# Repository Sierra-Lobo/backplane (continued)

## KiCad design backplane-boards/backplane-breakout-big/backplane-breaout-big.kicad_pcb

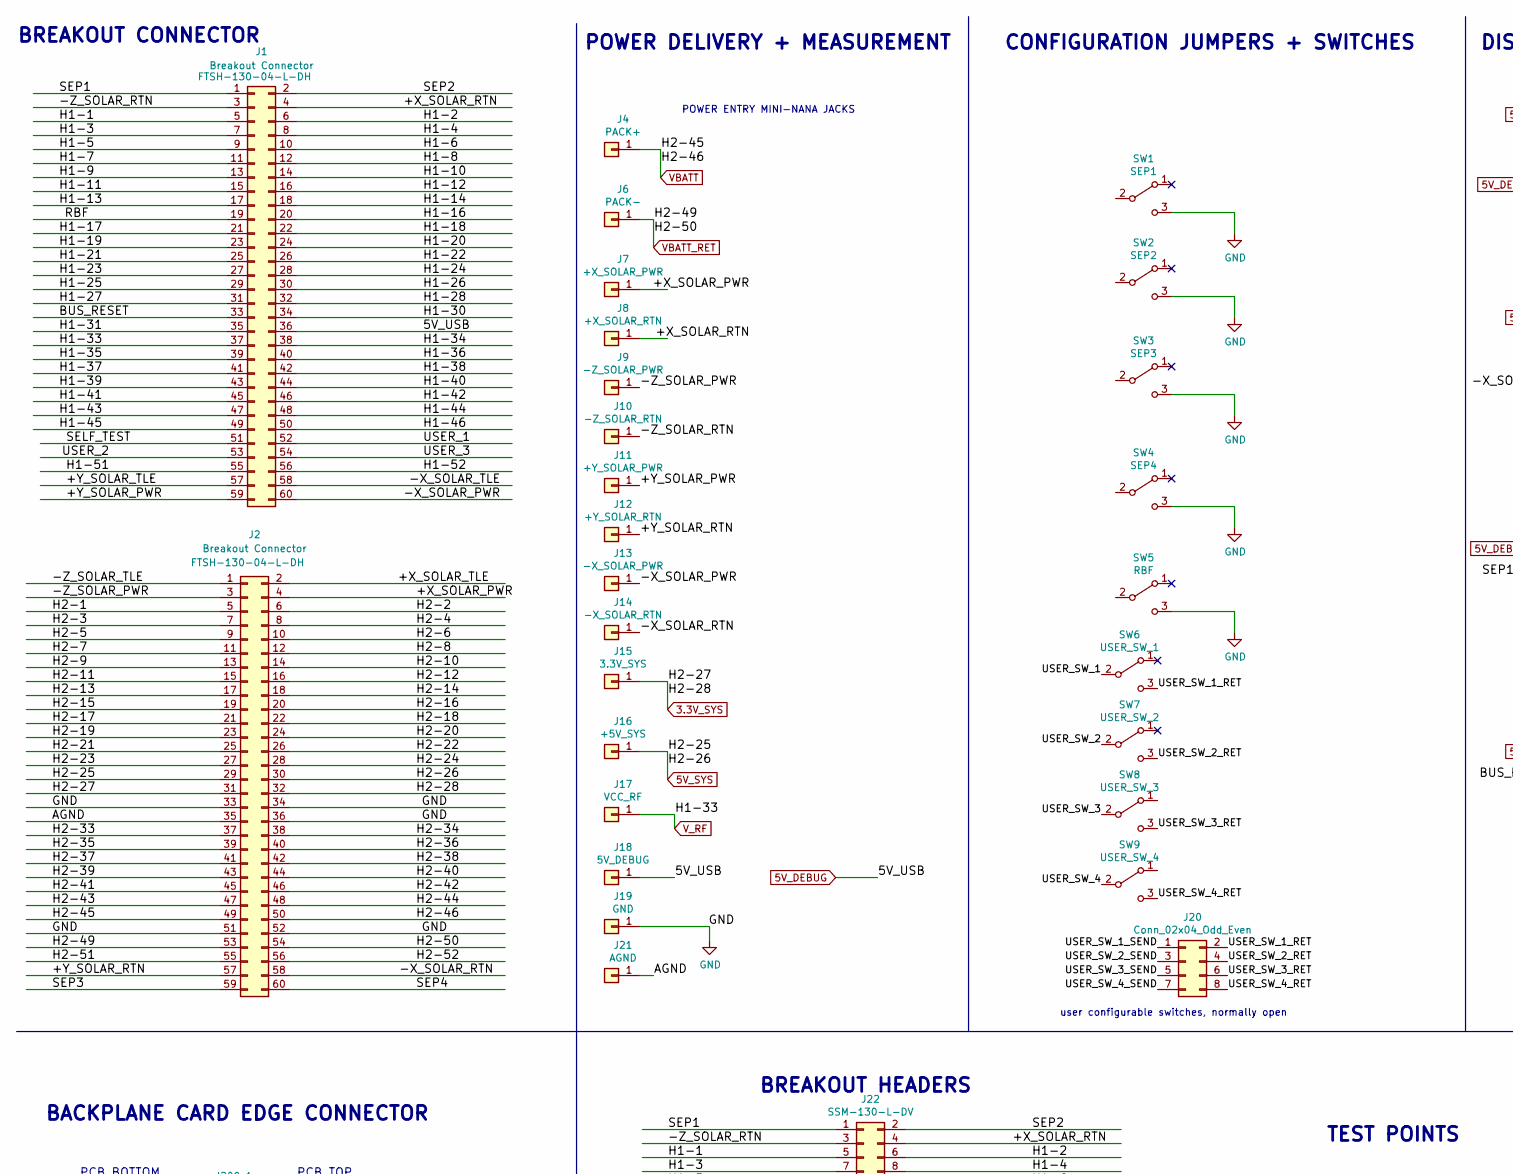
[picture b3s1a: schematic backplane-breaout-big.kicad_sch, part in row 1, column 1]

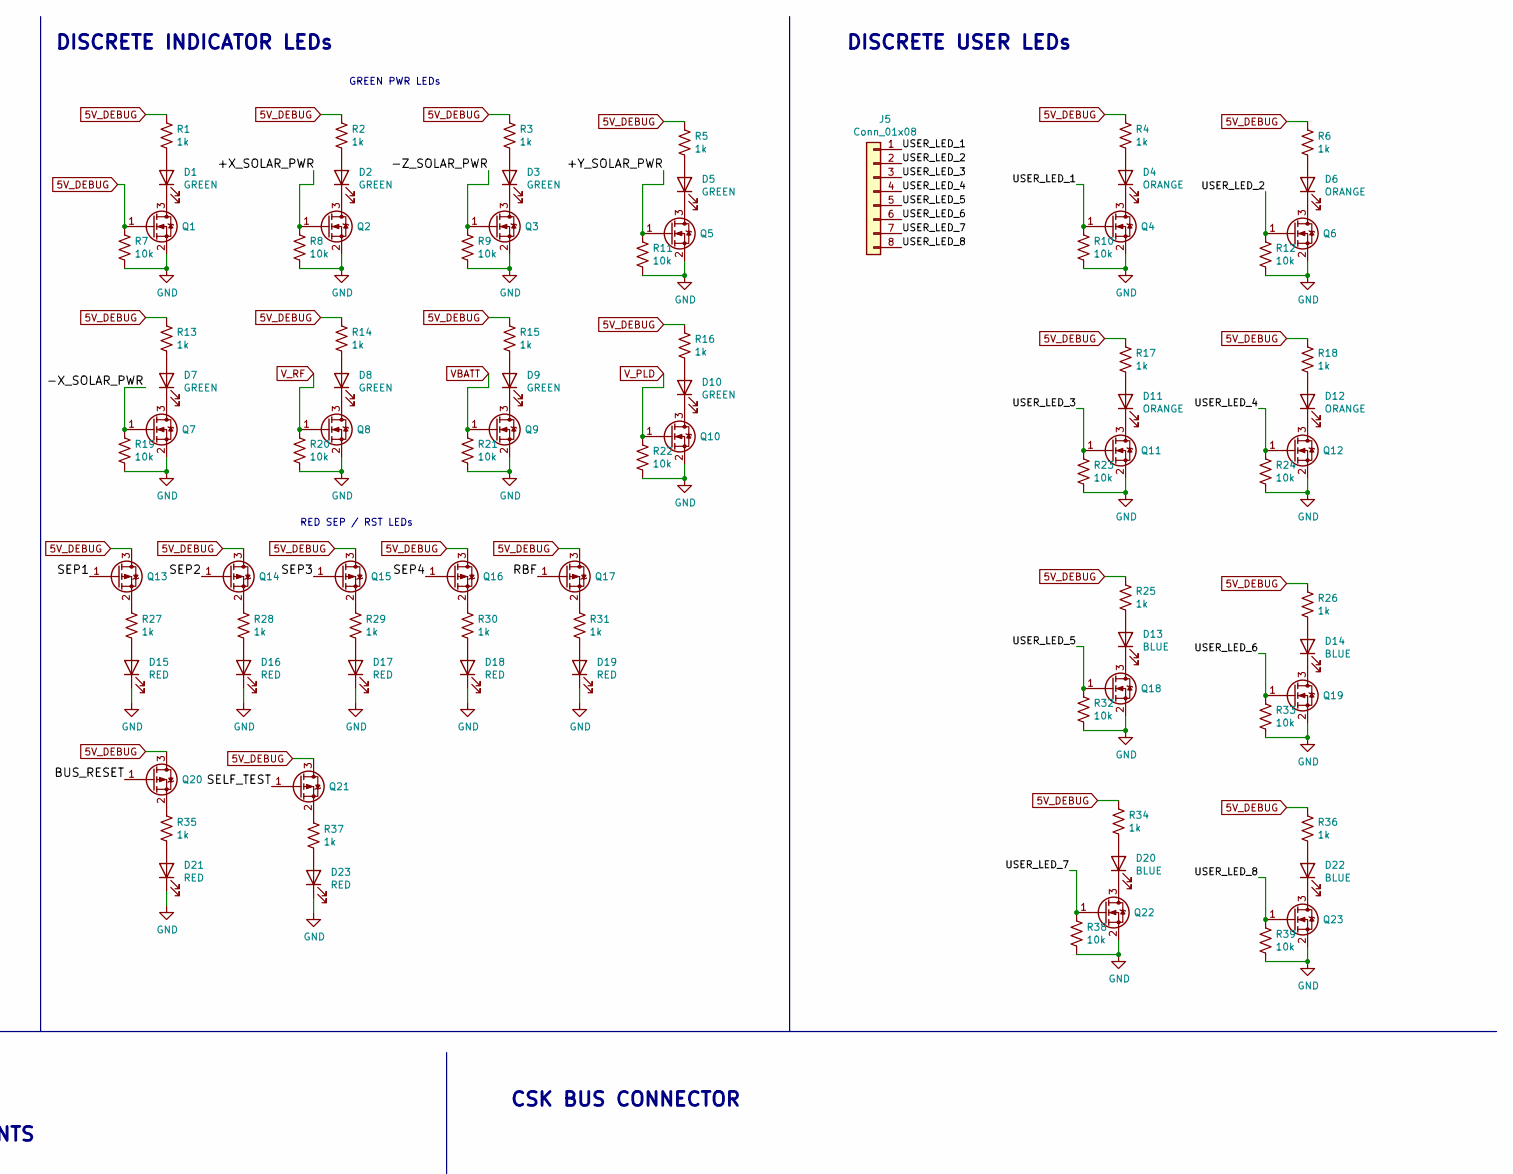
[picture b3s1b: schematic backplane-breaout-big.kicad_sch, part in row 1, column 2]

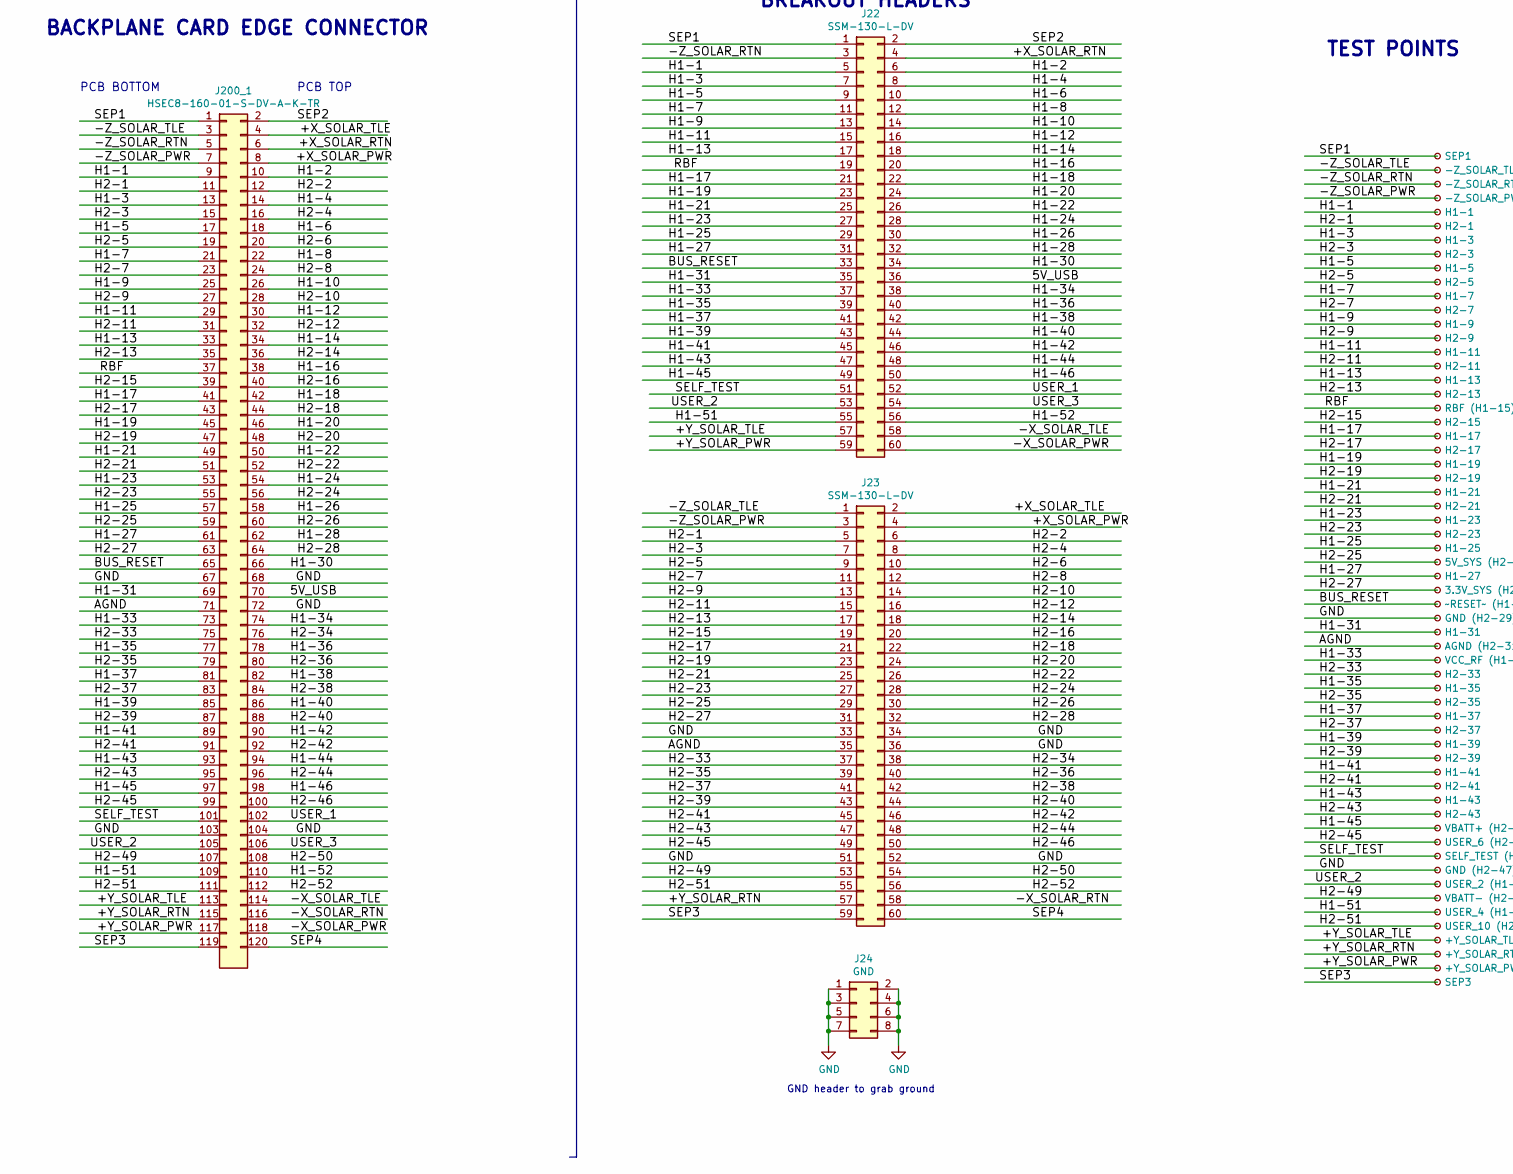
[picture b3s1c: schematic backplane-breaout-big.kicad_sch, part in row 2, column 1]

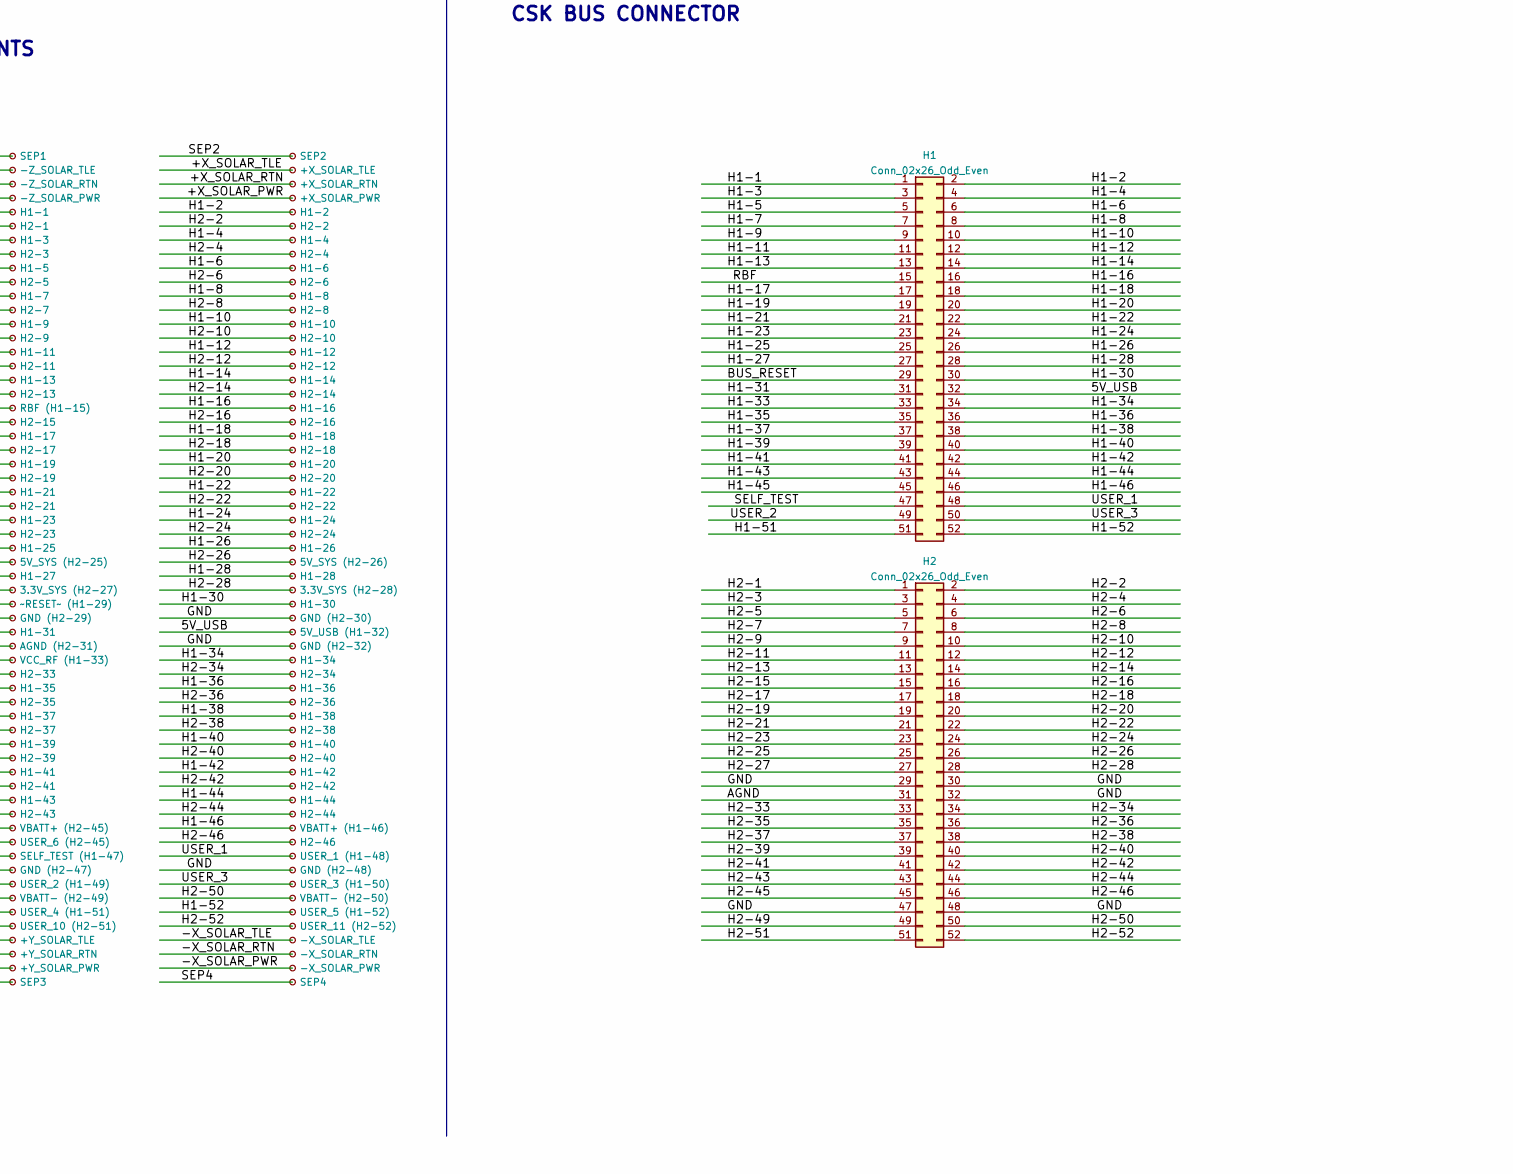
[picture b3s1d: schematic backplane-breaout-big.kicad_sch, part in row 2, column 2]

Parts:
D1, D2, D3, D5, D7, D8, D9, D10: GREEN; LED_0603_1608Metric_Castellated
D4, D6, D11, D12: ORANGE; LED_0603_1608Metric_Castellated
D13, D14, D20, D22: BLUE; LED_0603_1608Metric_Castellated
D15, D16, D17, D18, D19, D21, D23: RED; LED_0603_1608Metric_Castellated
H1, H2: Conn_02x26_Odd_Even; PinHeader_2x26_P2.54mm_Vertical
J1: Breakout Connector; SAMTEC_FTSH-130-04-L-DH; Manufacturer Part Numbe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 FTSH-130-04-L-DH
J2: Breakout Connector; SAMTEC_FTSH-130-04-L-DH_flipped; Manufacturer Part Numbe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 FTSH-130-04-L-DH
J4: PACK+; Keystone_476
J5: Conn_01x08; PinHeader_2x04_P2.54mm_Vertical_SMD
J6: PACK-; Keystone_476
J7: +X_SOLAR_PWR; Keystone_476
J8: +X_SOLAR_RTN; Keystone_476
J9: -Z_SOLAR_PWR; Keystone_476
J10: -Z_SOLAR_RTN; Keystone_476
J11: +Y_SOLAR_PWR; Keystone_476
J12: +Y_SOLAR_RTN; Keystone_476
J13: -X_SOLAR_PWR; Keystone_476
J14: -X_SOLAR_RTN; Keystone_476
J15: 3.3V_SYS; Keystone_476
J16: +5V_SYS; Keystone_476
J17: VCC_RF; Keystone_476
J18: 5V_DEBUG; Keystone_476
J19: GND; Keystone_476
J20: Conn_02x04_Odd_Even; PinHeader_2x04_P2.54mm_Vertical_SMD
J21: AGND; Keystone_476
J22, J23: SSM-130-L-DV; SAMTEC_SSM-130-L-DV
J24: GND; PinHeader_2x04_P2.54mm_Vertical_SMD
J200_1: HSEC8-160-01-S-DV-A-K-TR; Manufacturer Part Numbe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 HSEC8-160-01-S-DV-A-K-TR
Q1, Q2, Q3, Q4, Q5, Q6, Q7, Q8, Q9, Q10, Q11, Q12, Q18, Q19, Q22, Q23: DMG1012UW-7; SOT-323_SC-70
Q13, Q14, Q15, Q16, Q17, Q20, Q21: BSS84W-7-F; SOT-323_SC-70
R1, R2, R3, R4, R5, R6, R13, R14, R15, R16, R17, R18, R25, R26, R27, R28, R29, R30, R31, R34, R35, R36, R37: 1k; R_0603_1608Metric
R7, R8, R9, R10, R11, R12, R19, R20, R21, R22, R23, R24, R32, R33, R38, R39: 10k; R_0603_1608Metric
SW1: SEP1; JS102011SCQN
SW2: SEP2; JS102011SCQN
SW3: SEP3; JS102011SCQN
SW4: SEP4; JS102011SCQN
SW5: RBF; JS102011SCQN
SW6: USER_SW_1; JS102011SCQN
SW7: USER_SW_2; JS102011SCQN
SW8: USER_SW_3; JS102011SCQN
SW9: USER_SW_4; JS102011SCQN
TP1: SEP1; Keystone_5027
TP2: SEP2; Keystone_5027
TP3: -Z_SOLAR_TLE; Keystone_5027
TP4: +X_SOLAR_TLE; Keystone_5027
TP5: -Z_SOLAR_RTN; Keystone_5027
TP6: +X_SOLAR_RTN; Keystone_5027
TP7: -Z_SOLAR_PWR; Keystone_5027
TP8: +X_SOLAR_PWR; Keystone_5027
TP9: H1-1; Keystone_5027
TP10: H1-2; Keystone_5027
TP11: H2-1; Keystone_5027
TP12: H2-2; Keystone_5027
TP13: H1-3; Keystone_5027
TP14: H1-4; Keystone_5027
TP15: H2-3; Keystone_5027
TP16: H2-4; Keystone_5027
TP17: H1-5; Keystone_5027
TP18: H1-6; Keystone_5027
TP19: H2-5; Keystone_5027
TP20: H2-6; Keystone_5027
TP21: H1-7; Keystone_5027
TP22: H1-8; Keystone_5027
TP23: H2-7; Keystone_5027
TP24: H2-8; Keystone_5027
TP25: H1-9; Keystone_5027
TP26: H1-10; Keystone_5027
TP27: H2-9; Keystone_5027
TP28: H2-10; Keystone_5027
TP29: H1-11; Keystone_5027
TP30: H1-12; Keystone_5027
TP31: H2-11; Keystone_5027
TP32: H2-12; Keystone_5027
TP33: H1-13; Keystone_5027
TP34: H1-14; Keystone_5027
TP35: H2-13; Keystone_5027
TP36: H2-14; Keystone_5027
TP37: RBF (H1-15); Keystone_5027
TP38: H1-16; Keystone_5027
TP39: H2-15; Keystone_5027
TP40: H2-16; Keystone_5027
TP41: H1-17; Keystone_5027
TP42: H1-18; Keystone_5027
TP43: H2-17; Keystone_5027
TP44: H2-18; Keystone_5027
TP45: H1-19; Keystone_5027
TP46: H1-20; Keystone_5027
TP47: H2-19; Keystone_5027
TP48: H2-20; Keystone_5027
TP49: H1-21; Keystone_5027
TP50: H1-22; Keystone_5027
TP51: H2-21; Keystone_5027
TP52: H2-22; Keystone_5027
TP53: H1-23; Keystone_5027
TP54: H1-24; Keystone_5027
TP55: H2-23; Keystone_5027
TP56: H2-24; Keystone_5027
TP57: H1-25; Keystone_5027
TP58: H1-26; Keystone_5027
TP59: 5V_SYS (H2-25); Keystone_5027
TP60: 5V_SYS (H2-26); Keystone_5027
TP61: H1-27; Keystone_5027
TP62: H1-28; Keystone_5027
TP63: 3.3V_SYS (H2-27); Keystone_5027
TP64: 3.3V_SYS (H2-28); Keystone_5027
TP65: ~RESET~ (H1-29); Keystone_5027
TP66: H1-30; Keystone_5027
TP67: GND (H2-29); Keystone_5027
TP68: GND (H2-30); Keystone_5027
TP69: H1-31; Keystone_5027
TP70: 5V_USB (H1-32); Keystone_5027
TP71: AGND (H2-31); Keystone_5027
TP72: GND (H2-32); Keystone_5027
TP73: VCC_RF (H1-33); Keystone_5027
TP74: H1-34; Keystone_5027
TP75: H2-33; Keystone_5027
TP76: H2-34; Keystone_5027
TP77: H1-35; Keystone_5027
TP78: H1-36; Keystone_5027
TP79: H2-35; Keystone_5027
TP80: H2-36; Keystone_5027
TP81: H1-37; Keystone_5027
TP82: H1-38; Keystone_5027
TP83: H2-37; Keystone_5027
TP84: H2-38; Keystone_5027
TP85: H1-39; Keystone_5027
TP86: H1-40; Keystone_5027
TP87: H2-39; Keystone_5027
TP88: H2-40; Keystone_5027
TP89: H1-41; Keystone_5027
TP90: H1-42; Keystone_5027
TP91: H2-41; Keystone_5027
TP92: H2-42; Keystone_5027
TP93: H1-43; Keystone_5027
TP94: H1-44; Keystone_5027
TP95: H2-43; Keystone_5027
TP96: H2-44; Keystone_5027
TP97: VBATT+ (H2-45); Keystone_5027
TP98: VBATT+ (H1-46); Keystone_5027
TP99: USER_6 (H2-45); Keystone_5027
TP100: H2-46; Keystone_5027
TP101: SELF_TEST (H1-47); Keystone_5027
TP102: USER_1 (H1-48); Keystone_5027
TP103: GND (H2-47); Keystone_5027
TP104: GND (H2-48); Keystone_5027
TP105: USER_2 (H1-49); Keystone_5027
TP106: USER_3 (H1-50); Keystone_5027
TP107: VBATT- (H2-49); Keystone_5027
TP108: VBATT- (H2-50); Keystone_5027
TP109: USER_4 (H1-51); Keystone_5027
TP110: USER_5 (H1-52); Keystone_5027
TP111: USER_10 (H2-51); Keystone_5027
TP112: USER_11 (H2-52); Keystone_5027
TP113: +Y_SOLAR_TLE; Keystone_5027
TP114: -X_SOLAR_TLE; Keystone_5027
TP115: +Y_SOLAR_RTN; Keystone_5027
TP116: -X_SOLAR_RTN; Keystone_5027
TP117: +Y_SOLAR_PWR; Keystone_5027
TP118: -X_SOLAR_PWR; Keystone_5027
TP119: SEP3; Keystone_5027
TP120: SEP4; Keystone_5027

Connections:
3.3V_SYS: H2.27, H2.28, J2.31, J2.32, J15.1, J23.31, J23.32, J200_1.63, J200_1.64, TP63.1, TP64.1
5V_DEBUG: H1.32, J1.36, J18.1, J22.36, J200_1.70, Q1.1 (G), Q13.3 (D), Q14.3 (D), Q15.3 (D), Q16.3 (D), Q17.3 (D), Q20.3 (D), Q21.3 (D), R1.1, R2.1, R3.1, R4.1, R5.1, R6.1, R7.1, R13.1, R14.1, R15.1, R16.1, R17.1, R18.1, R25.1, R26.1, R34.1, R36.1, TP70.1
5V_SYS: H2.25, H2.26, J2.29, J2.30, J16.1, J23.29, J23.30, J200_1.59, J200_1.60, TP59.1, TP60.1
/+X_SOLAR_PWR: J2.4, J7.1, J23.4, J200_1.8, TP8.1
/+X_SOLAR_RTN: J1.4, J8.1, J22.4, J200_1.6, TP6.1
/+X_SOLAR_TLE: J2.2, J23.2, J200_1.4, TP4.1
/+Y_SOLAR_PWR: J1.59, J11.1, J22.59, J200_1.117, Q5.1 (G), R11.1, TP117.1
/+Y_SOLAR_RTN: J2.57, J12.1, J23.57, J200_1.115, TP115.1
/+Y_SOLAR_TLE: J1.57, J22.57, J200_1.113, TP113.1
/-X_SOLAR_PWR: J1.60, J13.1, J22.60, J200_1.118, Q7.1 (G), R19.1, TP118.1
/-X_SOLAR_RTN: J2.58, J14.1, J23.58, J200_1.116, TP116.1
/-X_SOLAR_TLE: J1.58, J22.58, J200_1.114, TP114.1
/-Z_SOLAR_PWR: J2.3, J9.1, J23.3, J200_1.7, Q3.1 (G), R9.1, TP7.1
/-Z_SOLAR_RTN: J1.3, J10.1, J22.3, J200_1.5, TP5.1
/-Z_SOLAR_TLE: J2.1, J23.1, J200_1.3, TP3.1
/AGND: H2.31, J2.35, J21.1, J23.35, J200_1.71, TP71.1
/BUS_RESET: H1.29, J1.33, J22.33, J200_1.65, Q20.1 (G), TP65.1
/H1-1: H1.1, J1.5, J22.5, J200_1.9, TP9.1
/H1-2: H1.2, J1.6, J22.6, J200_1.10, TP10.1
/H1-3: H1.3, J1.7, J22.7, J200_1.13, TP13.1
/H1-4: H1.4, J1.8, J22.8, J200_1.14, TP14.1
/H1-5: H1.5, J1.9, J22.9, J200_1.17, TP17.1
/H1-6: H1.6, J1.10, J22.10, J200_1.18, TP18.1
/H1-7: H1.7, J1.11, J22.11, J200_1.21, TP21.1
/H1-8: H1.8, J1.12, J22.12, J200_1.22, TP22.1
/H1-9: H1.9, J1.13, J22.13, J200_1.25, TP25.1
/H1-10: H1.10, J1.14, J22.14, J200_1.26, TP26.1
/H1-11: H1.11, J1.15, J22.15, J200_1.29, TP29.1
/H1-12: H1.12, J1.16, J22.16, J200_1.30, TP30.1
/H1-13: H1.13, J1.17, J22.17, J200_1.33, TP33.1
/H1-14: H1.14, J1.18, J22.18, J200_1.34, TP34.1
/H1-16: H1.16, J1.20, J22.20, J200_1.38, TP38.1
/H1-17: H1.17, J1.21, J22.21, J200_1.41, TP41.1
/H1-18: H1.18, J1.22, J22.22, J200_1.42, TP42.1
/H1-19: H1.19, J1.23, J22.23, J200_1.45, TP45.1
/H1-20: H1.20, J1.24, J22.24, J200_1.46, TP46.1
/H1-21: H1.21, J1.25, J22.25, J200_1.49, TP49.1
/H1-22: H1.22, J1.26, J22.26, J200_1.50, TP50.1
/H1-23: H1.23, J1.27, J22.27, J200_1.53, TP53.1
/H1-24: H1.24, J1.28, J22.28, J200_1.54, TP54.1
/H1-25: H1.25, J1.29, J22.29, J200_1.57, TP57.1
/H1-26: H1.26, J1.30, J22.30, J200_1.58, TP58.1
/H1-27: H1.27, J1.31, J22.31, J200_1.61, TP61.1
/H1-28: H1.28, J1.32, J22.32, J200_1.62, TP62.1
/H1-30: H1.30, J1.34, J22.34, J200_1.66, TP66.1
/H1-31: H1.31, J1.35, J22.35, J200_1.69, TP69.1
/H1-34: H1.34, J1.38, J22.38, J200_1.74, TP74.1
/H1-35: H1.35, J1.39, J22.39, J200_1.77, TP77.1
/H1-36: H1.36, J1.40, J22.40, J200_1.78, TP78.1
/H1-37: H1.37, J1.41, J22.41, J200_1.81, TP81.1
/H1-38: H1.38, J1.42, J22.42, J200_1.82, TP82.1
/H1-39: H1.39, J1.43, J22.43, J200_1.85, TP85.1
/H1-40: H1.40, J1.44, J22.44, J200_1.86, TP86.1
/H1-41: H1.41, J1.45, J22.45, J200_1.89, TP89.1
/H1-42: H1.42, J1.46, J22.46, J200_1.90, TP90.1
/H1-43: H1.43, J1.47, J22.47, J200_1.93 (Pin93), TP93.1
/H1-44: H1.44, J1.48, J22.48, J200_1.94, TP94.1
/H1-45: H1.45, J1.49, J22.49, J200_1.97, TP97.1
/H1-46: H1.46, J1.50, J22.50, J200_1.98, TP98.1
/H1-51: H1.51, J1.55, J22.55, J200_1.109, TP109.1
/H1-52: H1.52, J1.56, J22.56, J200_1.110, TP110.1
/H2-1: H2.1, J2.5, J23.5, J200_1.11, TP11.1
/H2-2: H2.2, J2.6, J23.6, J200_1.12, TP12.1
/H2-3: H2.3, J2.7, J23.7, J200_1.15, TP15.1
/H2-4: H2.4, J2.8, J23.8, J200_1.16, TP16.1
/H2-5: H2.5, J2.9, J23.9, J200_1.19, TP19.1
/H2-6: H2.6, J2.10, J23.10, J200_1.20, TP20.1
/H2-7: H2.7, J2.11, J23.11, J200_1.23, TP23.1
/H2-8: H2.8, J2.12, J23.12, J200_1.24, TP24.1
/H2-9: H2.9, J2.13, J23.13, J200_1.27, TP27.1
/H2-10: H2.10, J2.14, J23.14, J200_1.28, TP28.1
/H2-11: H2.11, J2.15, J23.15, J200_1.31, TP31.1
/H2-12: H2.12, J2.16, J23.16, J200_1.32, TP32.1
/H2-13: H2.13, J2.17, J23.17, J200_1.35, TP35.1
/H2-14: H2.14, J2.18, J23.18, J200_1.36, TP36.1
/H2-15: H2.15, J2.19, J23.19, J200_1.39, TP39.1
/H2-16: H2.16, J2.20, J23.20, J200_1.40, TP40.1
/H2-17: H2.17, J2.21, J23.21, J200_1.43, TP43.1
/H2-18: H2.18, J2.22, J23.22, J200_1.44, TP44.1
/H2-19: H2.19, J2.23, J23.23, J200_1.47, TP47.1
/H2-20: H2.20, J2.24, J23.24, J200_1.48, TP48.1
/H2-21: H2.21, J2.25, J23.25, J200_1.51, TP51.1
/H2-22: H2.22, J2.26, J23.26, J200_1.52, TP52.1
/H2-23: H2.23, J2.27, J23.27, J200_1.55, TP55.1
/H2-24: H2.24, J2.28, J23.28, J200_1.56, TP56.1
/H2-33: H2.33, J2.37, J23.37, J200_1.75, TP75.1
/H2-34: H2.34, J2.38, J23.38, J200_1.76, TP76.1
/H2-35: H2.35, J2.39, J23.39, J200_1.79, TP79.1
/H2-36: H2.36, J2.40, J23.40, J200_1.80, TP80.1
/H2-37: H2.37, J2.41, J23.41, J200_1.83, TP83.1
/H2-38: H2.38, J2.42, J23.42, J200_1.84, TP84.1
/H2-39: H2.39, J2.43, J23.43, J200_1.87, TP87.1
/H2-40: H2.40, J2.44, J23.44, J200_1.88, TP88.1
/H2-41: H2.41, J2.45, J23.45, J200_1.91, TP91.1
/H2-42: H2.42, J2.46, J23.46, J200_1.92, TP92.1
/H2-43: H2.43, J2.47, J23.47, J200_1.95, TP95.1
/H2-44: H2.44, J2.48, J23.48, J200_1.96, TP96.1
/H2-51: H2.51, J2.55, J23.55, J200_1.111, TP111.1
/H2-52: H2.52, J2.56, J23.56, J200_1.112, TP112.1
/RBF: H1.15, J1.19, J22.19, J200_1.37, Q17.1 (G), TP37.1
/SELF_TEST: H1.47, J1.51, J22.51, J200_1.101, Q21.1 (G), TP101.1
/SEP1: J1.1, J22.1, J200_1.1, Q13.1 (G), TP1.1
/SEP2: J1.2, J22.2, J200_1.2, Q14.1 (G), TP2.1
/SEP3: J2.59, J23.59, J200_1.119, Q15.1 (G), TP119.1
/SEP4: J2.60, J23.60, J200_1.120, Q16.1 (G), TP120.1
/USER_1: H1.48, J1.52, J22.52, J200_1.102, TP102.1
/USER_2: H1.49, J1.53, J22.53, J200_1.105, TP105.1
/USER_3: H1.50, J1.54, J22.54, J200_1.106, TP106.1
/USER_LED_1: J5.1, Q4.1 (G), R10.1
/USER_LED_2: J5.2, Q6.1 (G), R12.1
/USER_LED_3: J5.3, Q11.1 (G), R23.1
/USER_LED_4: J5.4, Q12.1 (G), R24.1
/USER_LED_5: J5.5, Q18.1 (G), R32.1
/USER_LED_6: J5.6, Q19.1 (G), R33.1
/USER_LED_7: J5.7, Q22.1 (G), R38.1
/USER_LED_8: J5.8, Q23.1 (G), R39.1
/USER_SW_1: SW6.2 (B)
/USER_SW_1_RET: J20.2, SW6.3 (C)
/USER_SW_1_SEND: J20.1
/USER_SW_2: SW7.2 (B)
/USER_SW_2_RET: J20.4, SW7.3 (C)
/USER_SW_2_SEND: J20.3
/USER_SW_3: SW8.2 (B)
/USER_SW_3_RET: J20.6, SW8.3 (C)
/USER_SW_3_SEND: J20.5
/USER_SW_4: SW9.2 (B)
/USER_SW_4_RET: J20.8, SW9.3 (C)
/USER_SW_4_SEND: J20.7
GND: D15.1 (K), D16.1 (K), D17.1 (K), D18.1 (K), D19.1 (K), D21.1 (K), D23.1 (K), H2.29, H2.30, H2.32, H2.47, H2.48, J2.33, J2.34, J2.36, J2.51, J2.52, J19.1, J23.33, J23.34, J23.36, J23.51, J23.52, J24.1, J24.2, J24.3, J24.4, J24.5, J24.6, J24.7, J24.8, J200_1.67, J200_1.68, J200_1.72, J200_1.103, J200_1.104, Q1.2 (S), Q2.2 (S), Q3.2 (S), Q4.2 (S), Q5.2 (S), Q6.2 (S), Q7.2 (S), Q8.2 (S), Q9.2 (S), Q10.2 (S), Q11.2 (S), Q12.2 (S), Q18.2 (S), Q19.2 (S), Q22.2 (S), Q23.2 (S), R7.2, R8.2, R9.2, R10.2, R11.2, R12.2, R19.2, R20.2, R21.2, R22.2, R23.2, R24.2, R32.2, R33.2, R38.2, R39.2, SW1.3 (C), SW2.3 (C), SW3.3 (C), SW4.3 (C), SW5.3 (C), TP67.1, TP68.1, TP72.1, TP103.1, TP104.1
unnamed: D1.1 (K), Q1.3 (D)
unnamed: D1.2 (A), R1.2
unnamed: D2.1 (K), Q2.3 (D)
unnamed: D2.2 (A), R2.2
unnamed: D3.1 (K), Q3.3 (D)
unnamed: D3.2 (A), R3.2
unnamed: D4.1 (K), Q4.3 (D)
unnamed: D4.2 (A), R4.2
unnamed: D5.1 (K), Q5.3 (D)
unnamed: D5.2 (A), R5.2
unnamed: D6.1 (K), Q6.3 (D)
unnamed: D6.2 (A), R6.2
unnamed: D7.1 (K), Q7.3 (D)
unnamed: D7.2 (A), R13.2
unnamed: D8.1 (K), Q8.3 (D)
unnamed: D8.2 (A), R14.2
unnamed: D9.1 (K), Q9.3 (D)
unnamed: D9.2 (A), R15.2
unnamed: D10.1 (K), Q10.3 (D)
unnamed: D10.2 (A), R16.2
unnamed: D11.1 (K), Q11.3 (D)
unnamed: D11.2 (A), R17.2
unnamed: D12.1 (K), Q12.3 (D)
unnamed: D12.2 (A), R18.2
unnamed: D13.1 (K), Q18.3 (D)
unnamed: D13.2 (A), R25.2
unnamed: D14.1 (K), Q19.3 (D)
unnamed: D14.2 (A), R26.2
unnamed: D15.2 (A), R27.2
unnamed: D16.2 (A), R28.2
unnamed: D17.2 (A), R29.2
unnamed: D18.2 (A), R30.2
unnamed: D19.2 (A), R31.2
unnamed: D20.1 (K), Q22.3 (D)
unnamed: D20.2 (A), R34.2
unnamed: D21.2 (A), R35.2
unnamed: D22.1 (K), Q23.3 (D)
unnamed: D22.2 (A), R36.2
unnamed: D23.2 (A), R37.2
unnamed: Q2.1 (G), R8.1
unnamed: Q13.2 (S), R27.1
unnamed: Q14.2 (S), R28.1
unnamed: Q15.2 (S), R29.1
unnamed: Q16.2 (S), R30.1
unnamed: Q17.2 (S), R31.1
unnamed: Q20.2 (S), R35.1
unnamed: Q21.2 (S), R37.1
VBATT: H2.45, H2.46, J2.49, J2.50, J4.1, J23.49, J23.50, J200_1.99, J200_1.100, Q9.1 (G), R21.1, TP99.1, TP100.1
VBATT_RET: H2.49, H2.50, J2.53, J2.54, J6.1, J23.53, J23.54, J200_1.107, J200_1.108, TP107.1, TP108.1
V_PLD: Q10.1 (G), R22.1
V_RF: H1.33, J1.37, J17.1, J22.37, J200_1.73, Q8.1 (G), R20.1, TP73.1

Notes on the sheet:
POWER DELIVERY + MEASUREMENT
BREAKOUT CONNECTOR
CONFIGURATION JUMPERS + SWITCHES
CSK BUS CONNECTOR
BACKPLANE CARD EDGE CONNECTOR
DISCRETE USER LEDs
DISCRETE INDICATOR LEDs
PCB TOP
PCB BOTTOM
GND header to grab ground
RED SEP / RST LEDs
BREAKOUT HEADERS
POWER ENTRY MINI-NANA JACKS
user configurable switches, normally open
GREEN PWR LEDs
TEST POINTS

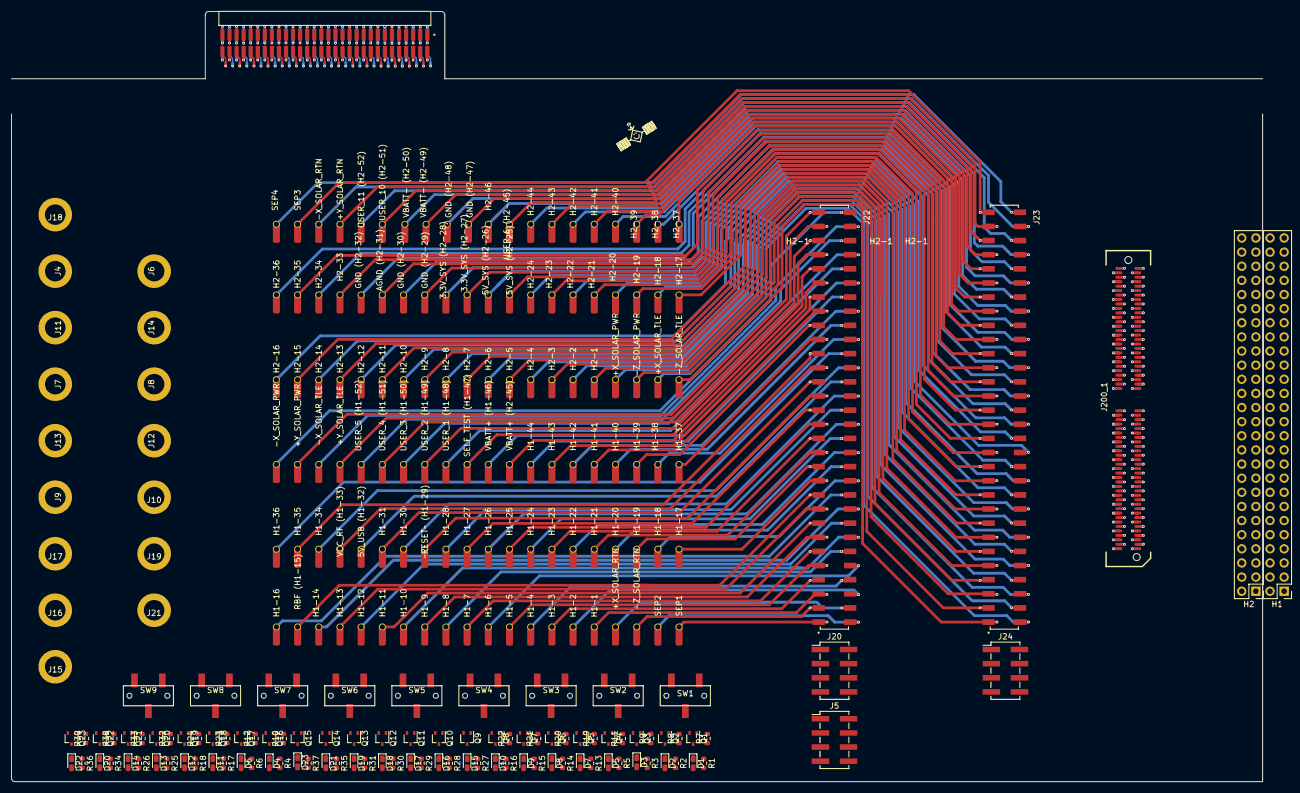
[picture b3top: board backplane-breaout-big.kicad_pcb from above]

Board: 6 copper layers, 224.9 x 138.5 mm, 240 parts (1 on the bottom side), 172 nets.

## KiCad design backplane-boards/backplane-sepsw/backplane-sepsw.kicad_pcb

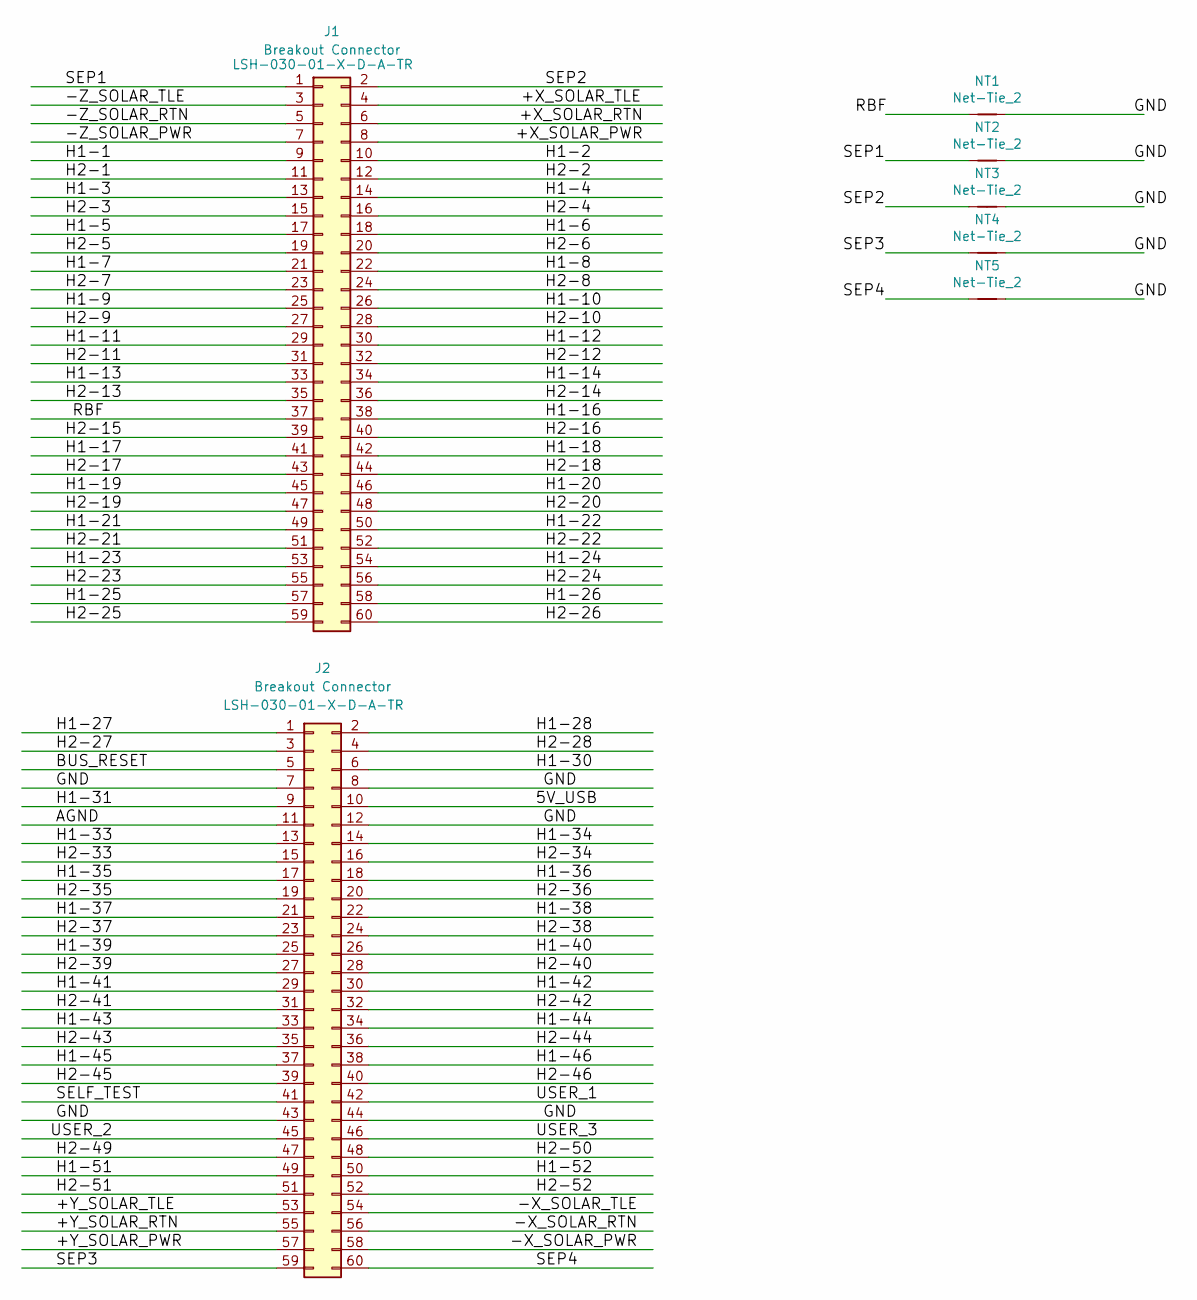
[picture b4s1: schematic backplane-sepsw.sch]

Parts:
J1, J2: Breakout Connector; SAMTEC_LSH-030-01-X-D-A-TR; Manufacturer Part Numbe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 LSH-030-01-X-D-A-TR
NT1, NT2, NT3, NT4, NT5: Net-Tie_2; NetTie-2_SMD_Pad0.25mm

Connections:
/5V_USB: J2.10
/+X_SOLAR_PWR: J1.8
/+X_SOLAR_RTN: J1.6
/+X_SOLAR_TLE: J1.4
/+Y_SOLAR_PWR: J2.57
/+Y_SOLAR_RTN: J2.55
/+Y_SOLAR_TLE: J2.53
/-X_SOLAR_PWR: J2.58
/-X_SOLAR_RTN: J2.56
/-X_SOLAR_TLE: J2.54
/-Z_SOLAR_PWR: J1.7
/-Z_SOLAR_RTN: J1.5
/-Z_SOLAR_TLE: J1.3
/AGND: J2.11
/BUS_RESET: J2.5
/GND: J2.7, J2.8, J2.12, J2.43, J2.44, NT1.2, NT2.2, NT3.2, NT4.2, NT5.2
/H1-1: J1.9
/H1-2: J1.10
/H1-3: J1.13
/H1-4: J1.14
/H1-5: J1.17
/H1-6: J1.18
/H1-7: J1.21
/H1-8: J1.22
/H1-9: J1.25
/H1-10: J1.26
/H1-11: J1.29
/H1-12: J1.30
/H1-13: J1.33
/H1-14: J1.34
/H1-16: J1.38
/H1-17: J1.41
/H1-18: J1.42
/H1-19: J1.45
/H1-20: J1.46
/H1-21: J1.49
/H1-22: J1.50
/H1-23: J1.53
/H1-24: J1.54
/H1-25: J1.57
/H1-26: J1.58
/H1-27: J2.1
/H1-28: J2.2
/H1-30: J2.6
/H1-31: J2.9
/H1-33: J2.13
/H1-34: J2.14
/H1-35: J2.17
/H1-36: J2.18
/H1-37: J2.21
/H1-38: J2.22
/H1-39: J2.25
/H1-40: J2.26
/H1-41: J2.29
/H1-42: J2.30
/H1-43: J2.33
/H1-44: J2.34
/H1-45: J2.37
/H1-46: J2.38
/H1-51: J2.49
/H1-52: J2.50
/H2-1: J1.11
/H2-2: J1.12
/H2-3: J1.15
/H2-4: J1.16
/H2-5: J1.19
/H2-6: J1.20
/H2-7: J1.23
/H2-8: J1.24
/H2-9: J1.27
/H2-10: J1.28
/H2-11: J1.31
/H2-12: J1.32
/H2-13: J1.35
/H2-14: J1.36
/H2-15: J1.39
/H2-16: J1.40
/H2-17: J1.43
/H2-18: J1.44
/H2-19: J1.47
/H2-20: J1.48
/H2-21: J1.51
/H2-22: J1.52
/H2-23: J1.55
/H2-24: J1.56
/H2-25: J1.59
/H2-26: J1.60
/H2-27: J2.3
/H2-28: J2.4
/H2-33: J2.15
/H2-34: J2.16
/H2-35: J2.19
/H2-36: J2.20
/H2-37: J2.23
/H2-38: J2.24
/H2-39: J2.27
/H2-40: J2.28
/H2-41: J2.31
/H2-42: J2.32
/H2-43: J2.35
/H2-44: J2.36
/H2-45: J2.39
/H2-46: J2.40
/H2-49: J2.47
/H2-50: J2.48
/H2-51: J2.51
/H2-52: J2.52
/RBF: J1.37, NT1.1
/SELF_TEST: J2.41
/SEP1: J1.1, NT2.1
/SEP2: J1.2, NT3.1
/SEP3: J2.59, NT4.1
/SEP4: J2.60, NT5.1
/USER_1: J2.42
/USER_2: J2.45
/USER_3: J2.46

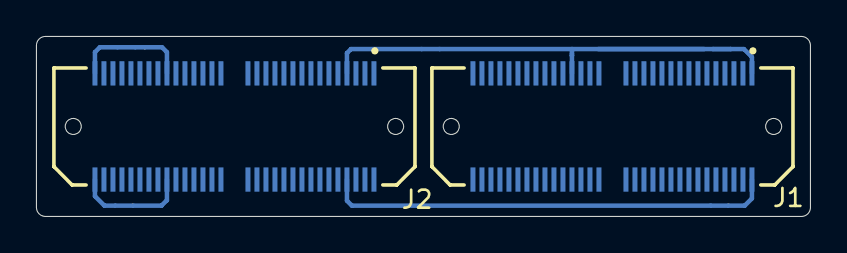
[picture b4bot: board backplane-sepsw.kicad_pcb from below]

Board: 2 copper layers, 43.0 x 10.0 mm, 7 parts (7 on the bottom side), 6 nets.

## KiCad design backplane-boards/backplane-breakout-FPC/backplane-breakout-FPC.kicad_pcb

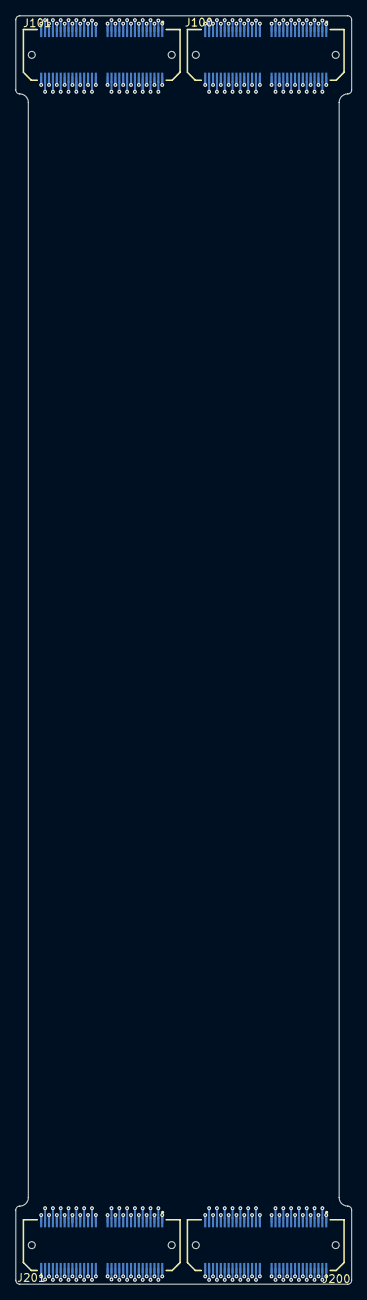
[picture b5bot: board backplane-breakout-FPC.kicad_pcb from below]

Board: 6 copper layers, 43.0 x 162.4 mm, 4 parts (4 on the bottom side), 116 nets.

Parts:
J100, J101, J200, J201: Breakout Connector; SAMTEC_LSH-030-01-X-D-A-TR

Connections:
/5V_USB: J101.10, J201.10
/+X_SOLAR_PWR: J100.8, J200.8
/+X_SOLAR_RTN: J100.6, J200.6
/+X_SOLAR_TLE: J100.4, J200.4
/+Y_SOLAR_PWR: J101.57, J201.57
/+Y_SOLAR_RTN: J101.55, J201.55
/+Y_SOLAR_TLE: J101.53, J201.53
/-X_SOLAR_PWR: J101.58, J201.58
/-X_SOLAR_RTN: J101.56, J201.56
/-X_SOLAR_TLE: J101.54, J201.54
/-Z_SOLAR_PWR: J100.7, J200.7
/-Z_SOLAR_RTN: J100.5, J200.5
/-Z_SOLAR_TLE: J100.3, J200.3
/AGND: J101.11, J201.11
/BUS_RESET: J101.5, J201.5
/GND: J101.7, J101.8, J101.12, J101.43, J101.44, J201.7, J201.8, J201.12, J201.43, J201.44
/H1-1: J100.9, J200.9
/H1-2: J100.10, J200.10
/H1-3: J100.13, J200.13
/H1-4: J100.14, J200.14
/H1-5: J100.17, J200.17
/H1-6: J100.18, J200.18
/H1-7: J100.21, J200.21
/H1-8: J100.22, J200.22
/H1-9: J100.25, J200.25
/H1-10: J100.26, J200.26
/H1-11: J100.29, J200.29
/H1-12: J100.30, J200.30
/H1-13: J100.33, J200.33
/H1-14: J100.34, J200.34
/H1-16: J100.38, J200.38
/H1-17: J100.41, J200.41
/H1-18: J100.42, J200.42
/H1-19: J100.45, J200.45
/H1-20: J100.46, J200.46
/H1-21: J100.49, J200.49
/H1-22: J100.50, J200.50
/H1-23: J100.53, J200.53
/H1-24: J100.54, J200.54
/H1-25: J100.57, J200.57
/H1-26: J100.58, J200.58
/H1-27: J101.1, J201.1
/H1-28: J101.2, J201.2
/H1-30: J101.6, J201.6
/H1-31: J101.9, J201.9
/H1-33: J101.13, J201.13
/H1-34: J101.14, J201.14
/H1-35: J101.17, J201.17
/H1-36: J101.18, J201.18
/H1-37: J101.21, J201.21
/H1-38: J101.22, J201.22
/H1-39: J101.25, J201.25
/H1-40: J101.26, J201.26
/H1-41: J101.29, J201.29
/H1-42: J101.30, J201.30
/H1-43: J101.33, J201.33
/H1-44: J101.34, J201.34
/H1-45: J101.37, J201.37
/H1-46: J101.38, J201.38
/H1-51: J101.49, J201.49
/H1-52: J101.50, J201.50
/H2-1: J100.11, J200.11
/H2-2: J100.12, J200.12
/H2-3: J100.15, J200.15
/H2-4: J100.16, J200.16
/H2-5: J100.19, J200.19
/H2-6: J100.20, J200.20
/H2-7: J100.23, J200.23
/H2-8: J100.24, J200.24
/H2-9: J100.27, J200.27
/H2-10: J100.28, J200.28
/H2-11: J100.31, J200.31
/H2-12: J100.32, J200.32
/H2-13: J100.35, J200.35
/H2-14: J100.36, J200.36
/H2-15: J100.39, J200.39
/H2-16: J100.40, J200.40
/H2-17: J100.43, J200.43
/H2-18: J100.44, J200.44
/H2-19: J100.47, J200.47
/H2-20: J100.48, J200.48
/H2-21: J100.51, J200.51
/H2-22: J100.52, J200.52
/H2-23: J100.55, J200.55
/H2-24: J100.56, J200.56
/H2-25: J100.59, J200.59
/H2-26: J100.60, J200.60
/H2-27: J101.3, J201.3
/H2-28: J101.4, J201.4
/H2-33: J101.15, J201.15
/H2-34: J101.16, J201.16
/H2-35: J101.19, J201.19
/H2-36: J101.20, J201.20
/H2-37: J101.23, J201.23
/H2-38: J101.24, J201.24
/H2-39: J101.27, J201.27
/H2-40: J101.28, J201.28
/H2-41: J101.31, J201.31
/H2-42: J101.32, J201.32
/H2-43: J101.35, J201.35
/H2-44: J101.36, J201.36
/H2-45: J101.39, J201.39
/H2-46: J101.40, J201.40
/H2-49: J101.47, J201.47
/H2-50: J101.48, J201.48
/H2-51: J101.51, J201.51
/H2-52: J101.52, J201.52
/RBF: J100.37, J200.37
/SELF_TEST: J101.41, J201.41
/SEP1: J100.1, J200.1
/SEP2: J100.2, J200.2
/SEP3: J101.59, J201.59
/SEP4: J101.60, J201.60
/USER_1: J101.42, J201.42
/USER_2: J101.45, J201.45
/USER_3: J101.46, J201.46

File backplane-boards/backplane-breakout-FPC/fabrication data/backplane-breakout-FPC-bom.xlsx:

Reference | Quantity | Footprint | Manufacturer Part Number 1
J100, J101, J200, J201 | 4 | backplane-rbf:SAMTEC_LSH-030-01-X-D-A-TR | LSH-030-01-X-D-A-TR
